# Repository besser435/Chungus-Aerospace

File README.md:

# Chungus-Aerospace
For the model rockets made by my friend and myself.
Most of the code was written before I knew how to code/keep it maintainable, which is why pretty much everything is terrible.

chung

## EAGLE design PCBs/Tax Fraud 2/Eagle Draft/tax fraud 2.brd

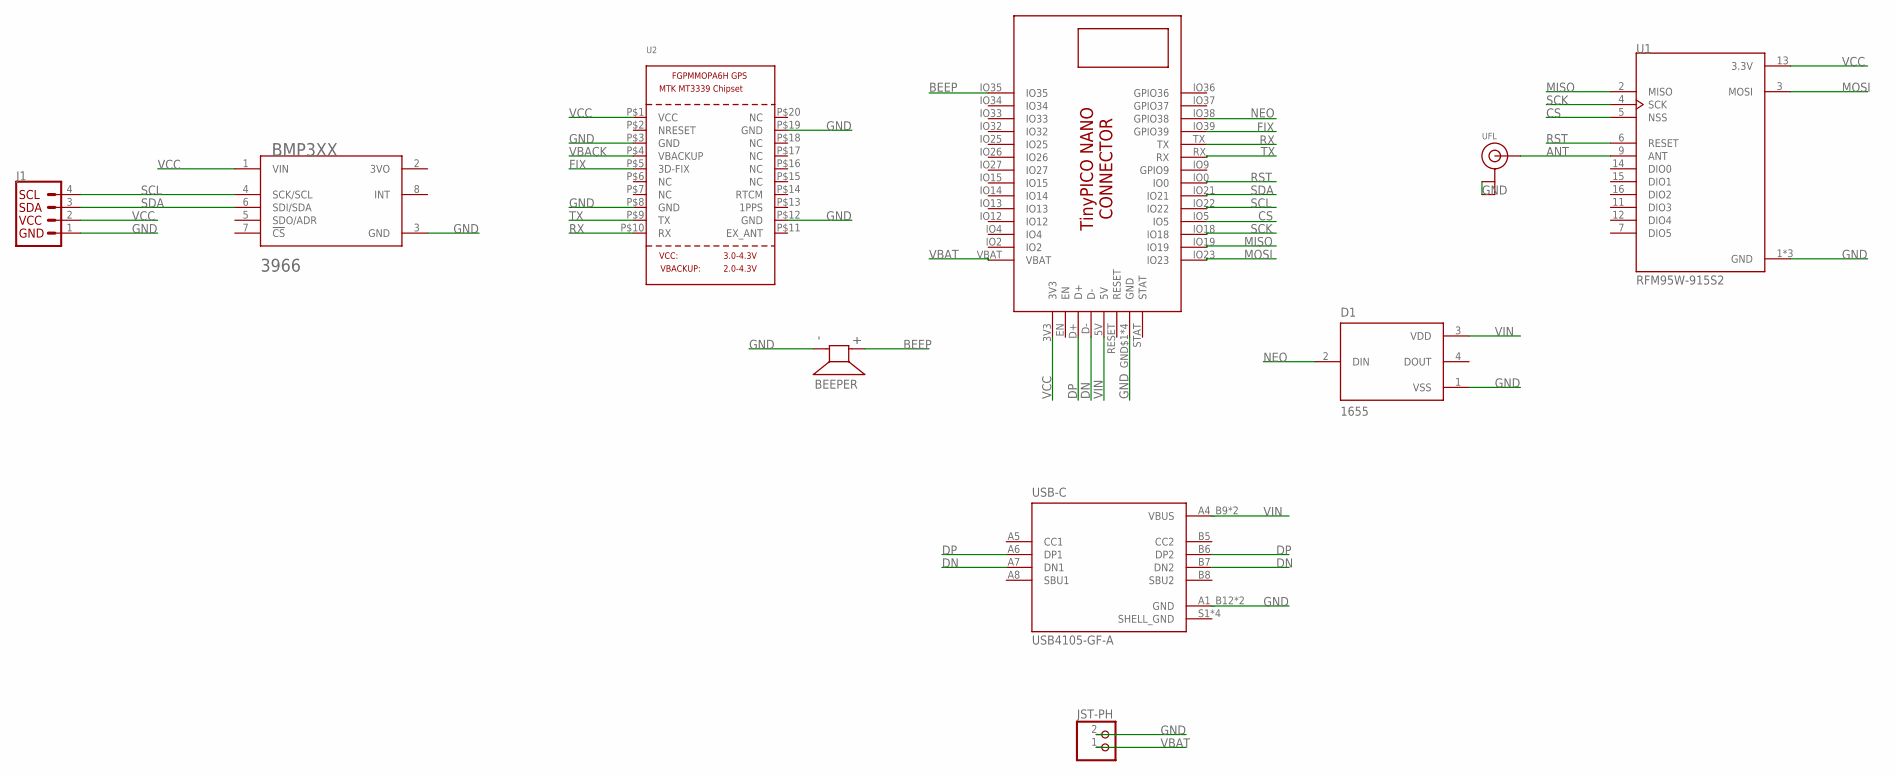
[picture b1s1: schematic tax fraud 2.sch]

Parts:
BEEPER: AI-1223-TWT-12V-R; XDCR_AI-1223-TWT-12V-R
BMP3XX: ADAFRUIT_INDUSTRIES_3966ADAFRUIT_INDUSTRIES_3966_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; ADAFRUIT_INDUSTRIES_3966_0
D1: 1655; LED_1655
J1: QWIIC_CONNECTORJS-1MM; 1X04_1MM_RA
JST-PH: JST_2PIN-SMT-RA; JST-PH-2-SMT-RA
U1: RFM95W-915S2; XCVR_RFM95W-915S2
U2: GPS_FGPMMOPA6H; FGPMMOPA6H
U$1: TINYPICO-NANO-CONNECTOR
UFL: ANTENNA_U.FL; U.FL
USB-C: USB4105-GF-A; GCT_USB4105-GF-A

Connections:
3VO: BMP3XX.2 (3VO)
ANT: U1.9 (ANT), UFL.3 (SIGNAL)
BEEP: BEEPER.P (+), U$1.IO35
CS: U1.5 (NSS), U$1.IO5
DN: U$1.D-, USB-C.A7 (DN1), USB-C.B7 (DN2)
DP: U$1.D+, USB-C.A6 (DP1), USB-C.B6 (DP2)
FIX: U2.P$5 (3D-FIX), U$1.IO39 (GPIO39)
GND: BEEPER.N (-), BMP3XX.3 (GND), D1.1 (VSS), J1.1 (GND), JST-PH.2 (1), U1.1 (GND), U1.8 (GND), U1.10 (GND), U2.P$3 (GND), U2.P$8 (GND), U2.P$12 (GND), U2.P$19 (GND), U$1.GND$1 (GND), U$1.GND$2 (GND), U$1.GND$3 (GND), U$1.GND$4 (GND), UFL.1 (GND), UFL.2 (GND), USB-C.A1_B12 (GND), USB-C.B1_A12 (GND)
MISO: U1.2 (MISO), U$1.IO19
MOSI: U1.3 (MOSI), U$1.IO23
NEO: D1.2 (DIN), U$1.IO38 (GPIO38)
RST: U1.6 (RESET), U$1.IO0
RX: U2.P$10 (RX), U$1.TX
SCK: U1.4 (SCK), U$1.IO18
SCL: BMP3XX.4 (SCK/SCL), J1.4 (SCL), U$1.IO22
SDA: BMP3XX.6 (SDI/SDA), J1.3 (SDA), U$1.IO21
SHELL_GND: USB-C.S1 (SHELL_GND), USB-C.S2 (SHELL_GND), USB-C.S3 (SHELL_GND), USB-C.S4 (SHELL_GND)
TX: U2.P$9 (TX), U$1.RX
VBACK: U2.P$4 (VBACKUP)
VBAT: JST-PH.1 (2), U$1.VBAT
VCC: BMP3XX.1 (VIN), J1.2 (VCC), U1.13 (3.3V), U2.P$1 (VCC), U$1.3V3
VIN: D1.3 (VDD), U$1.5V, USB-C.A4_B9 (VBUS), USB-C.B4_A9 (VBUS)

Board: 2 copper layers, 10 parts (6 on the bottom side), 20 nets, no tracks yet.

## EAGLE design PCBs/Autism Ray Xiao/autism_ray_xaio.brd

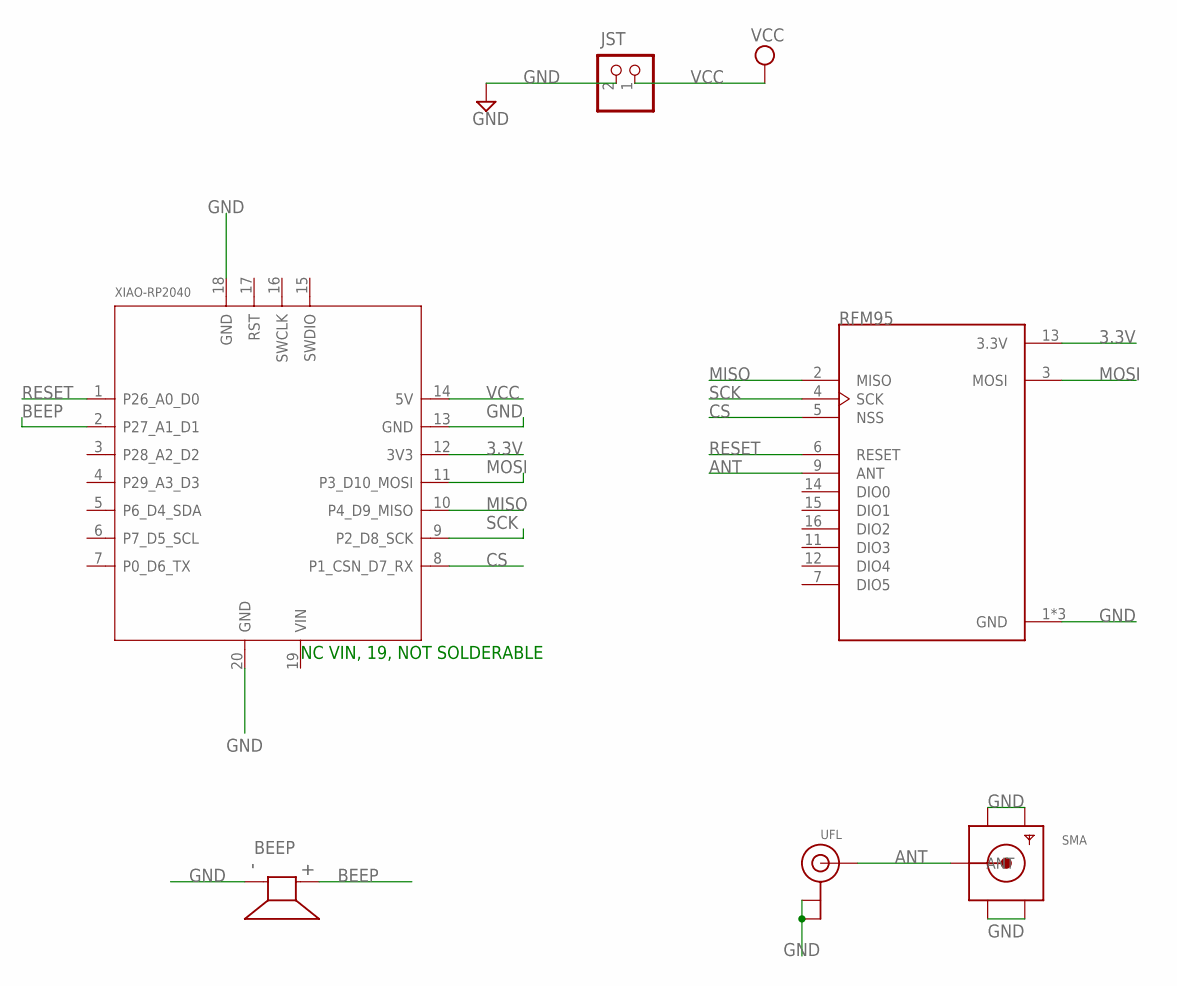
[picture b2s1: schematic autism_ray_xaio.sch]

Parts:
BEEP: AI-1223-TWT-12V-R; XDCR_AI-1223-TWT-12V-R
JST: JST_2PIN-SMT-RA; JST-PH-2-SMT-RA
RFM95: RFM95W-915S2; XCVR_RFM95W-915S2
SMA: SMACONNECTOR_EDGE; SMA_EDGELAUNCH
UFL: ANTENNA_U.FL; U.FL
XIAO-RP2040: XIAO-RP2040; XIAO-SAMD21/RP2040-MODULE14P-2.54-21X17.8MM

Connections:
3.3V: RFM95.13 (3.3V), XIAO-RP2040.12 (3V3)
ANT: RFM95.9 (ANT), SMA.P (ANT), UFL.3 (SIGNAL)
BEEP: BEEP.P (+), XIAO-RP2040.2 (P27_A1_D1)
CS: RFM95.5 (NSS), XIAO-RP2040.8 (P1_CSN_D7_RX)
GND: BEEP.N (-), JST.2 (1), RFM95.1 (GND), RFM95.8 (GND), RFM95.10 (GND), SMA.GND@1 (GND4), SMA.GND@2 (GND3), SMA.GND@3 (GND2), SMA.GND@4 (GND1), UFL.1 (GND), UFL.2 (GND), XIAO-RP2040.13 (GND), XIAO-RP2040.18 (GND), XIAO-RP2040.20 (GND)
MISO: RFM95.2 (MISO), XIAO-RP2040.10 (P4_D9_MISO)
MOSI: RFM95.3 (MOSI), XIAO-RP2040.11 (P3_D10_MOSI)
RESET: RFM95.6 (RESET), XIAO-RP2040.1 (P26_A0_D0)
SCK: RFM95.4 (SCK), XIAO-RP2040.9 (P2_D8_SCK)
VCC: JST.1 (2), XIAO-RP2040.14 (5V)

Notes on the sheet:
NC VIN, 19, NOT SOLDERABLE

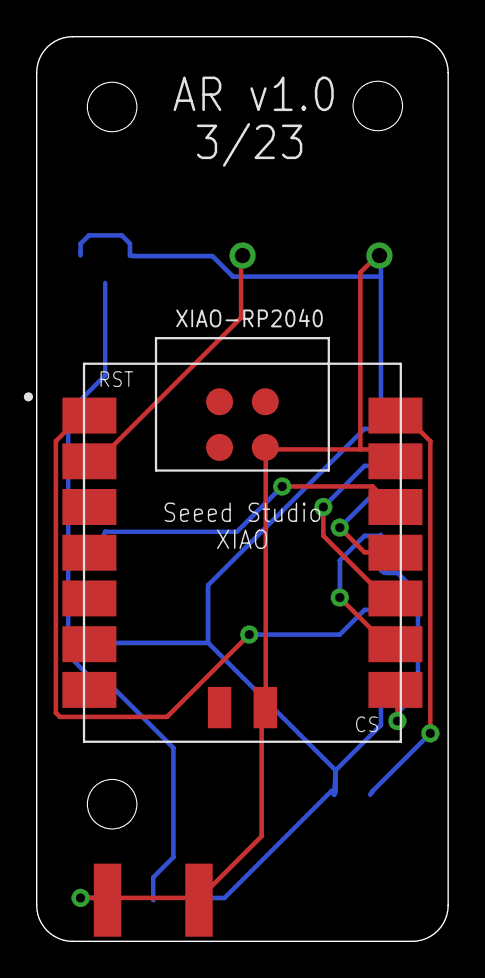
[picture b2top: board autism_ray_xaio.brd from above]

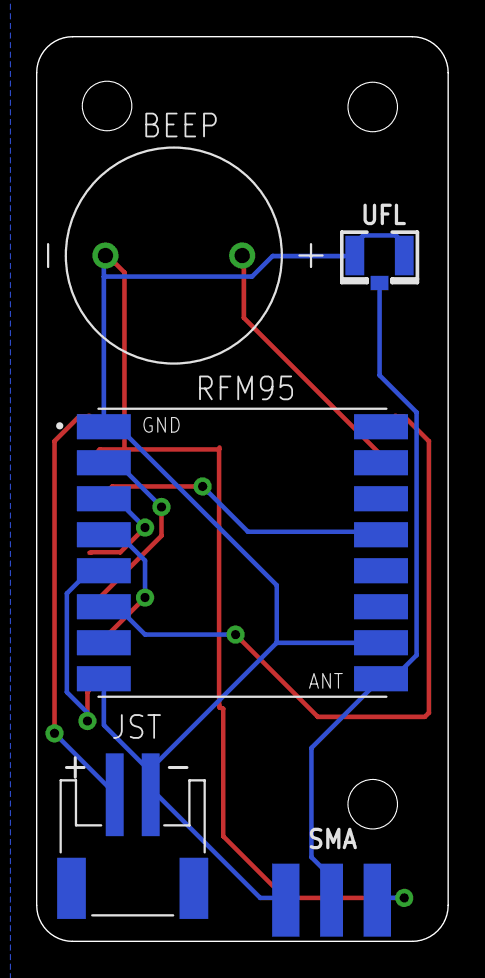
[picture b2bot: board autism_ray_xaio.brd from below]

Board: 2 copper layers, 22.9 x 50.3 mm, 6 parts (5 on the bottom side), 10 nets.

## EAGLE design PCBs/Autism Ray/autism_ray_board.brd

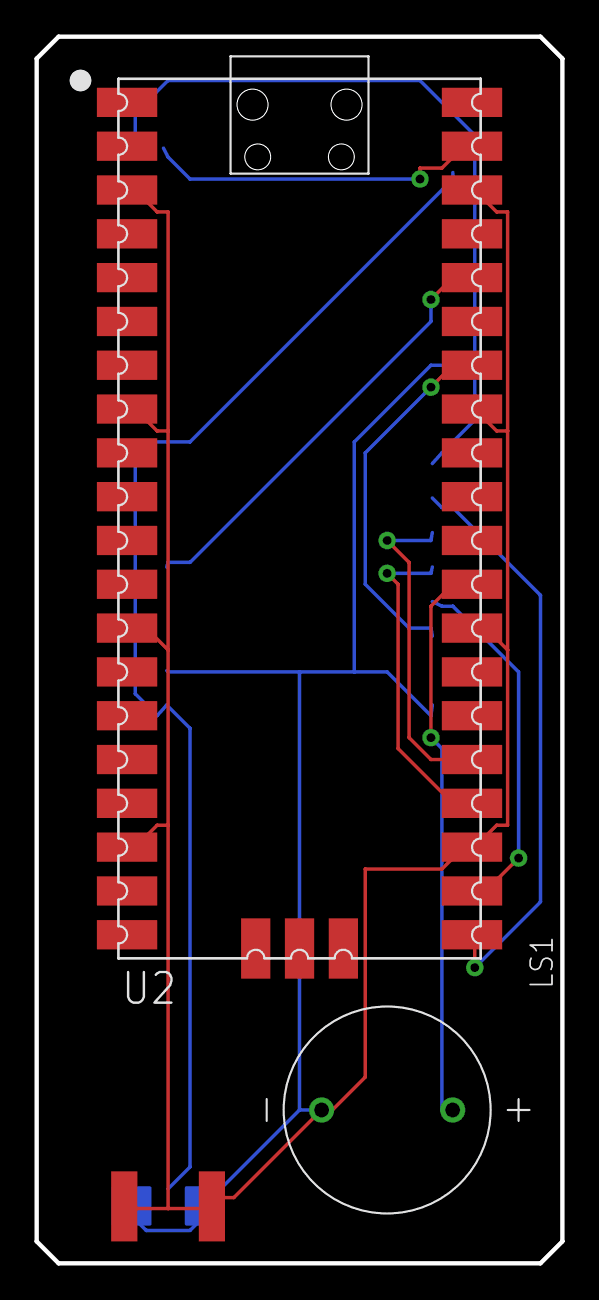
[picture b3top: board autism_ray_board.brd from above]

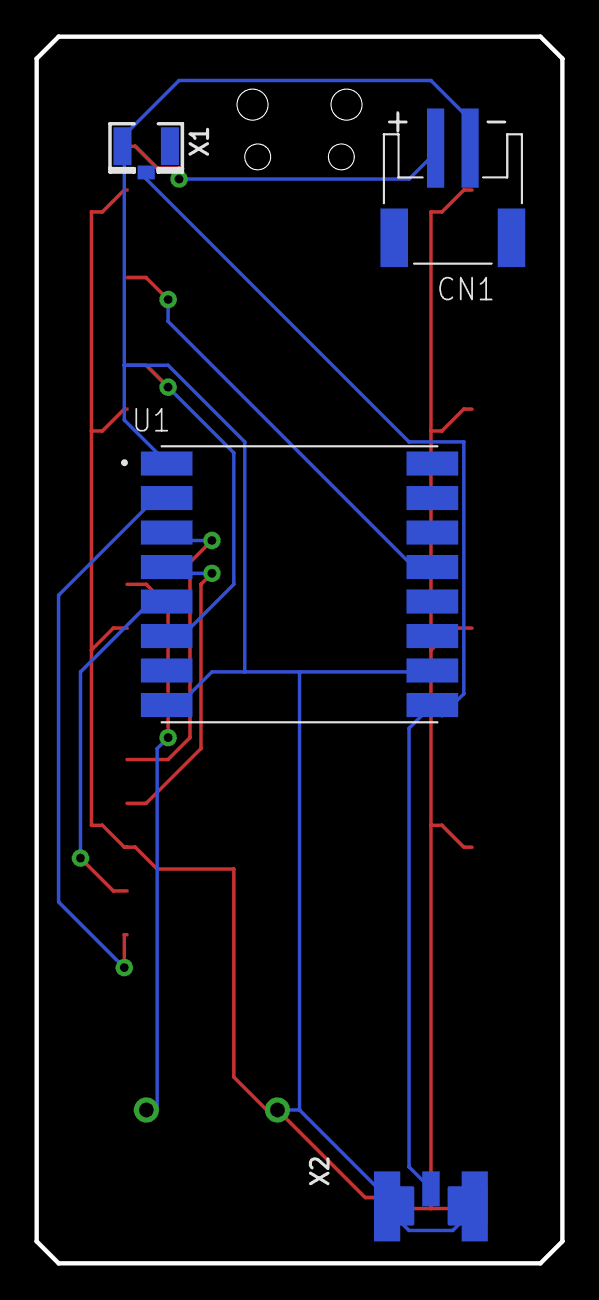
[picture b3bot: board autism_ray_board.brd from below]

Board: 2 copper layers, 30.5 x 71.1 mm, 6 parts (4 on the bottom side), 10 nets.

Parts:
CN1: JST-PH-2-SMT-RA
LS1: AI-1223-TWT-12V-R; XDCR_AI-1223-TWT-12V-R
U1: RFM95W-915S2; XCVR_RFM95W-915S2
U2: RASPBERRY_PICOSMD; PICO-PKG-SMD
X1: U.FL
X2: SMA_EDGELAUNCH_UFL

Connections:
3.3V: U1.13, U2.P$36
ANT: U1.9, X1.3, X2.P
BEEP: LS1.P, U2.P$29
CS: U1.5, U2.P$22
GND: CN1.2, LS1.N, U1.1, U1.8, U1.10, U2.P$3, U2.P$8, U2.P$13, U2.P$18, U2.P$23, U2.P$28, U2.P$33, U2.P$38, X1.2, X2.GND@1, X2.GND@2, X2.GND@3, X2.GND@4
MISO: U1.2, U2.P$21
MOSI: U1.3, U2.P$25
RST: U1.6, U2.P$34
SCK: U1.4, U2.P$24
VCC: CN1.1, U2.P$39

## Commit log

2021-12-29 chung
2021-12-29 v0.1
2021-12-31 v0.2
2021-12-31 borrowed project
    Hippity hoppity your code is now my property
2022-01-05 v0.2.1
    Added possible chute deploy code
2022-01-06 Added Feather Libraries
2022-01-06 v0.2.3
2022-01-08 v1.0
2022-01-09 v1.0.1
2022-01-12 v1.1
    debunged a few things
2022-01-12 legacy code
    This used to be required, but we changed how the code works. Because of this we don't need this bit anymore. I'm just uploading it incase we do need it again for whatever reason. We didn't write this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
2022-01-12 moved files
2022-01-12 Delete Feather-M4 Flight Telemetry Software.py
    Renamed to code.py so its easier to work with on the Feather.
2022-01-12 v1.2
2022-01-12 moved
2022-01-12 v1.3
2022-01-13 v1.1.1
2022-01-13 Our flight logs go here
2022-01-14 v1.1
2022-01-14 v1.4
2022-01-15 v1.5
2022-01-15 v0.1.1
2022-01-15 Why did I even make this
2022-01-16 1-15-22
2022-01-19 ooga booga
2022-01-19 v0.1.2
2022-01-19 test
2022-01-20 Committed to wrong part
2022-01-20 Name changes
2022-01-20 did the thing again
2022-01-20 File name change
2022-01-20 Updating files
2022-01-20 Clarified file names
2022-01-20 v1.6
2022-01-20 v0.1.3
2022-01-21 debugging logs for logging issue
2022-01-21 v1.7
2022-01-24 v1.8
2022-01-25 v1.8.1
2022-01-25 Updated directory structure
2022-01-25 Create why
2022-01-26 v1.9
2022-02-02 v2.2-alpha.1
2022-02-03 v2.0-alpha.2.3
    File and version name changes
2022-02-06 Adding untested MPIM parts
    Gotta make sure all the parts work together before committing to the main branch. Maybe even an operational flight.
2022-02-08 v1.10
2022-02-08 I will not make this a pull request
2022-02-09 Redoing RUD
2022-02-09 v2.0-alpha.3
2022-02-12 Updated tolerances a little
    It was wiggling around a little bit, so I made the tolerances a bit tighter to hopefully fix that.
2022-02-12 this part sucks lol
2022-02-16 v2.0-alpha.4
2022-02-17 CALC v2.0-alpha.5
2022-02-17 v1.10.2
2022-02-17 add CALCv1 mounts
2022-02-23 v1.11
2022-03-04 v2.0-alpha.6
2022-03-05 Moved MPIM stuff around, added 49mm MPIM
2022-03-14 v2.0-beta.1
2022-03-17 v1.12
2022-03-20 v2.0-beta.2
2022-03-22 v2.0-beta.3
2022-03-29 Not needed anymore
2022-04-06 v1.13
2022-04-06 v1.1.2
2022-04-08 v2.0-beta.4
2022-04-28 4-27-22
2022-05-04 init
2022-05-05 v2.0-beta.5
2022-05-15 More dual deployment parts
    Added a small 37.6x60mm avionics bay, bulkhead/coupler with space for wires and a pyro charge, 50mm long body tube for drogueless dual deployment, and a motor mount part that I forgot to add a while 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
2022-06-18 Transition to flyaway rod guide
    24x70mm only though, the 18mm ones are obsolete anyway
2022-07-05 updated lib
2022-07-06 flight
2022-07-14 Challenger ejection charge software v0.1
2022-07-21 First set of Full Send parts
2022-07-28 debung
2022-07-30 v1.2.1
2022-08-02 Updated Full Send
2022-08-20 v2.0-beta.6
2022-09-08 v1.14
2022-11-13 QT py velocity v0
    Now takes 30 seconds to reach FTL speeds instead of 3
    Also organized the clusterfuck of a QT py folder
2022-11-14 v1.1
    Made the code a bit neater
2022-11-14 v1.1 (#7)
    Made the code a bit neater
2022-11-20 Made integral less stupid
    Still untested, could very well be totally fucked, but it's definitely better than before
2022-11-20 Made variables less stupid and more readable
2022-11-21 defuck (#8)
    * Made integral less stupid
    * Made variables less stupid and more readable
2022-12-16 Fuller Send aerostructure
    .stl files and .csv file for the nose cone
2022-12-19 moved CALCv2
2022-12-25 v1.15-alpha.1
2022-12-25 Removed useless files
2022-12-25 Create code.py
    (Still untested, apparently I'm supposed to spend time with my family or something)
2022-12-30 Full accelerometer calibration, velocity logging
    I hate this
2022-12-31 Accelerometer calibration (#10)
    * Create code.py
    (Still untested, apparently I'm supposed to spend time with my family or something)
    * Full accelerometer calibration, velocity logging
    I hate this
    * Update code.py
    * Update code.py
2022-12-31 update file structure
2022-12-31 v1.15-beta.1
2022-12-31 v1.15
2023-01-03 v1.0-alpha.1
2023-03-01 Create Autism Ray PCB
2023-03-02 Update PCB
2023-03-02 Before ground pour
2023-03-02 Actaully before ground pour
2023-03-02 Actually after ground pour
2023-03-02 Update gitignore
2023-03-04 Update Eagle libraries
2023-03-09 Added XIAO lib
2023-03-15 Autosaves
2023-03-16 TF2 autosave
2023-03-17 Yagi hardware + calibration slight defuck
2023-03-19 Create thick parts
2023-03-19 v2.0-beta.7
2023-03-25 Tax Fraud v2 PCB
2023-03-25 Update autism_ray_xaio.b##
2023-04-12 Create TVC logic.py
    Needs more work. Idk how to reference specific elements in the array yet, but it's a start.
2023-04-13 TVC logic quat normalization + Euler
    Hopefully added code for normalizing the quaternion, and calculating one of the Euler angles. It should be possible to do a sanity check with this.
2023-04-14 TVC Euler math
    Finished Euler angle conversion math
2023-04-29 v1.0.2
    Rename to avoid linting errors in VS Code
2023-05-10 v1.0.3
2023-05-13 2020 rail/38mm launch tower parts
2023-05-14 Create BasicKalmanTest.py
    File for Kalman filter testing, no idea if it'll work
2023-05-28 v.1.1
2023-06-06 FS2 Avbay
2023-06-07 FS2 full avbay assembly
2023-06-08 FS2 avbay tolerance fix
    Defucked OD from 38.6mm to 38mm
2023-06-09 FS2 motor block
2023-06-29 FS2 motor blovck defuck i think
    I changed something maybe a week ago and forgot to commit lol
2023-06-29 FS2 29mm adapter
2023-07-01 TVC configuration
    something something conflicted file idk seems fine to me
2023-07-01 TVC configuration defuck
2023-07-02 Improved calibration
    Print formatting, gyro calibration, range defuck, renamed variables, kalman filter test that I completely forgot about
2023-07-02 stupid fucking radian conversion + format defuck
2023-07-06 7-6-23 launch
2023-07-11 Accelerometer velocity potential defuck
    Created cfg setup and new velocity logic that integrates first before getting the magnitude of the velocity vector.
2023-07-24 TVC logic setup (#11)
    * Create TVC logic.py
    Needs more work. Idk how to reference specific elements in the array yet, but it's a start.
    * TVC logic quat normalization + Euler
    Hopefully added code for normalizing the quaternion, and calculating one of the Euler angles. It should be possible to do a sanity check with this.
    * TVC Euler math
    Finished Euler angle conversion math
2023-07-24 TVC changes
2023-07-25 TVC array error possible defuck #2
2023-07-28 TVC/Accel logic defuck #3 (final)
    Modified TVC logic so it actually fucking works, cleaned it up and added comments so it's more readable, improved calibration, added PID constants to TVC config file for use in future features
2023-08-07 TVC body tube + nose cone generator
2023-09-15 TVC rocket body + QoL changes
    Updated TVC rocket body, changed frequency formula for autism ray ground software, unfucked nose cone generator math
2023-10-27 Rename, start landed function
2023-10-27 v1.3
    Add exit() in while True loop under keyboardInterrupt, fix HB text cutoff
2023-12-21 Remove old stuff
2024-01-26 v1.4: add display info, add cron job comment
2024-01-30 chunglib tvc 1
2024-01-30 FS2/TVC defuck?????
2024-01-30 chunglib tvc 1 (#12)
2024-02-03 Add UART test stuff
2024-02-07 Add initial AR2 tests
2024-02-14 Rev B - Fix UART pins
2024-02-14 Rev B - Improve ground plane
2024-02-14 Continue work on AR2
2024-02-16 git commit in case sussy house fire
    I am scared of data loss okay
2024-02-20 Update AR2 stuff
2024-02-23 AR2 updates
2024-03-04 Update AR2
2024-03-05 I am going insane
2024-03-07 Change out stupid fucking display library for an amazing one
2024-03-08 Update AR2, mostly functional now
2024-03-09 Change boot behavior, add alert display function
2024-03-20 Change fix quality to 3D indicator
2024-03-26 Blink on send to save power, add/fix comments
2024-04-04 Add power saving features, start on proper logging
2024-04-06 v1.2 - Reduce power by ~20mA
2024-04-06 v1.2.1 - Further reduce power draw
2024-05-15 Some software changes
2024-05-15 Create ChungRF
2024-05-15 Rename to ChungRF
2024-05-17 Update ChungRF
2024-05-20 Fix impedance
2024-05-24 Finalize design, add gerbers
2024-06-12 Update ChungRF, add software tests
2024-06-25 Last R1
2024-06-25 Add ESP32-S3-MINI
2024-06-28 ChungRF R2
2024-07-17 Add ChungRF tests
2024-07-17 Add MP SX126x lib (doesnt work)
2024-07-23 Update ChungRF tests
2024-10-07 turn good_sound into a class
2024-10-10 Add stop function, make second pin optional
2024-10-21 Fix ChungRF software
2024-10-21 ChungRF R3
2024-10-25 Clean Tracks, add Gerber files
2024-11-14 ChungRF R4 - Fix GNSS I2C bus
2024-11-14 Reorganize ChungRF stuff confirm the radios work
2024-11-27 Clean up stuff
2025-03-19 change some minor things
2025-03-19 Change to continuous listening (make it actually work)

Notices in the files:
parts and their libraries:
SparkFun-Connectors: Licensing: Creative Commons ShareAlike 4.0 International - https://creativecommons.org/licenses/by-sa/4.0
